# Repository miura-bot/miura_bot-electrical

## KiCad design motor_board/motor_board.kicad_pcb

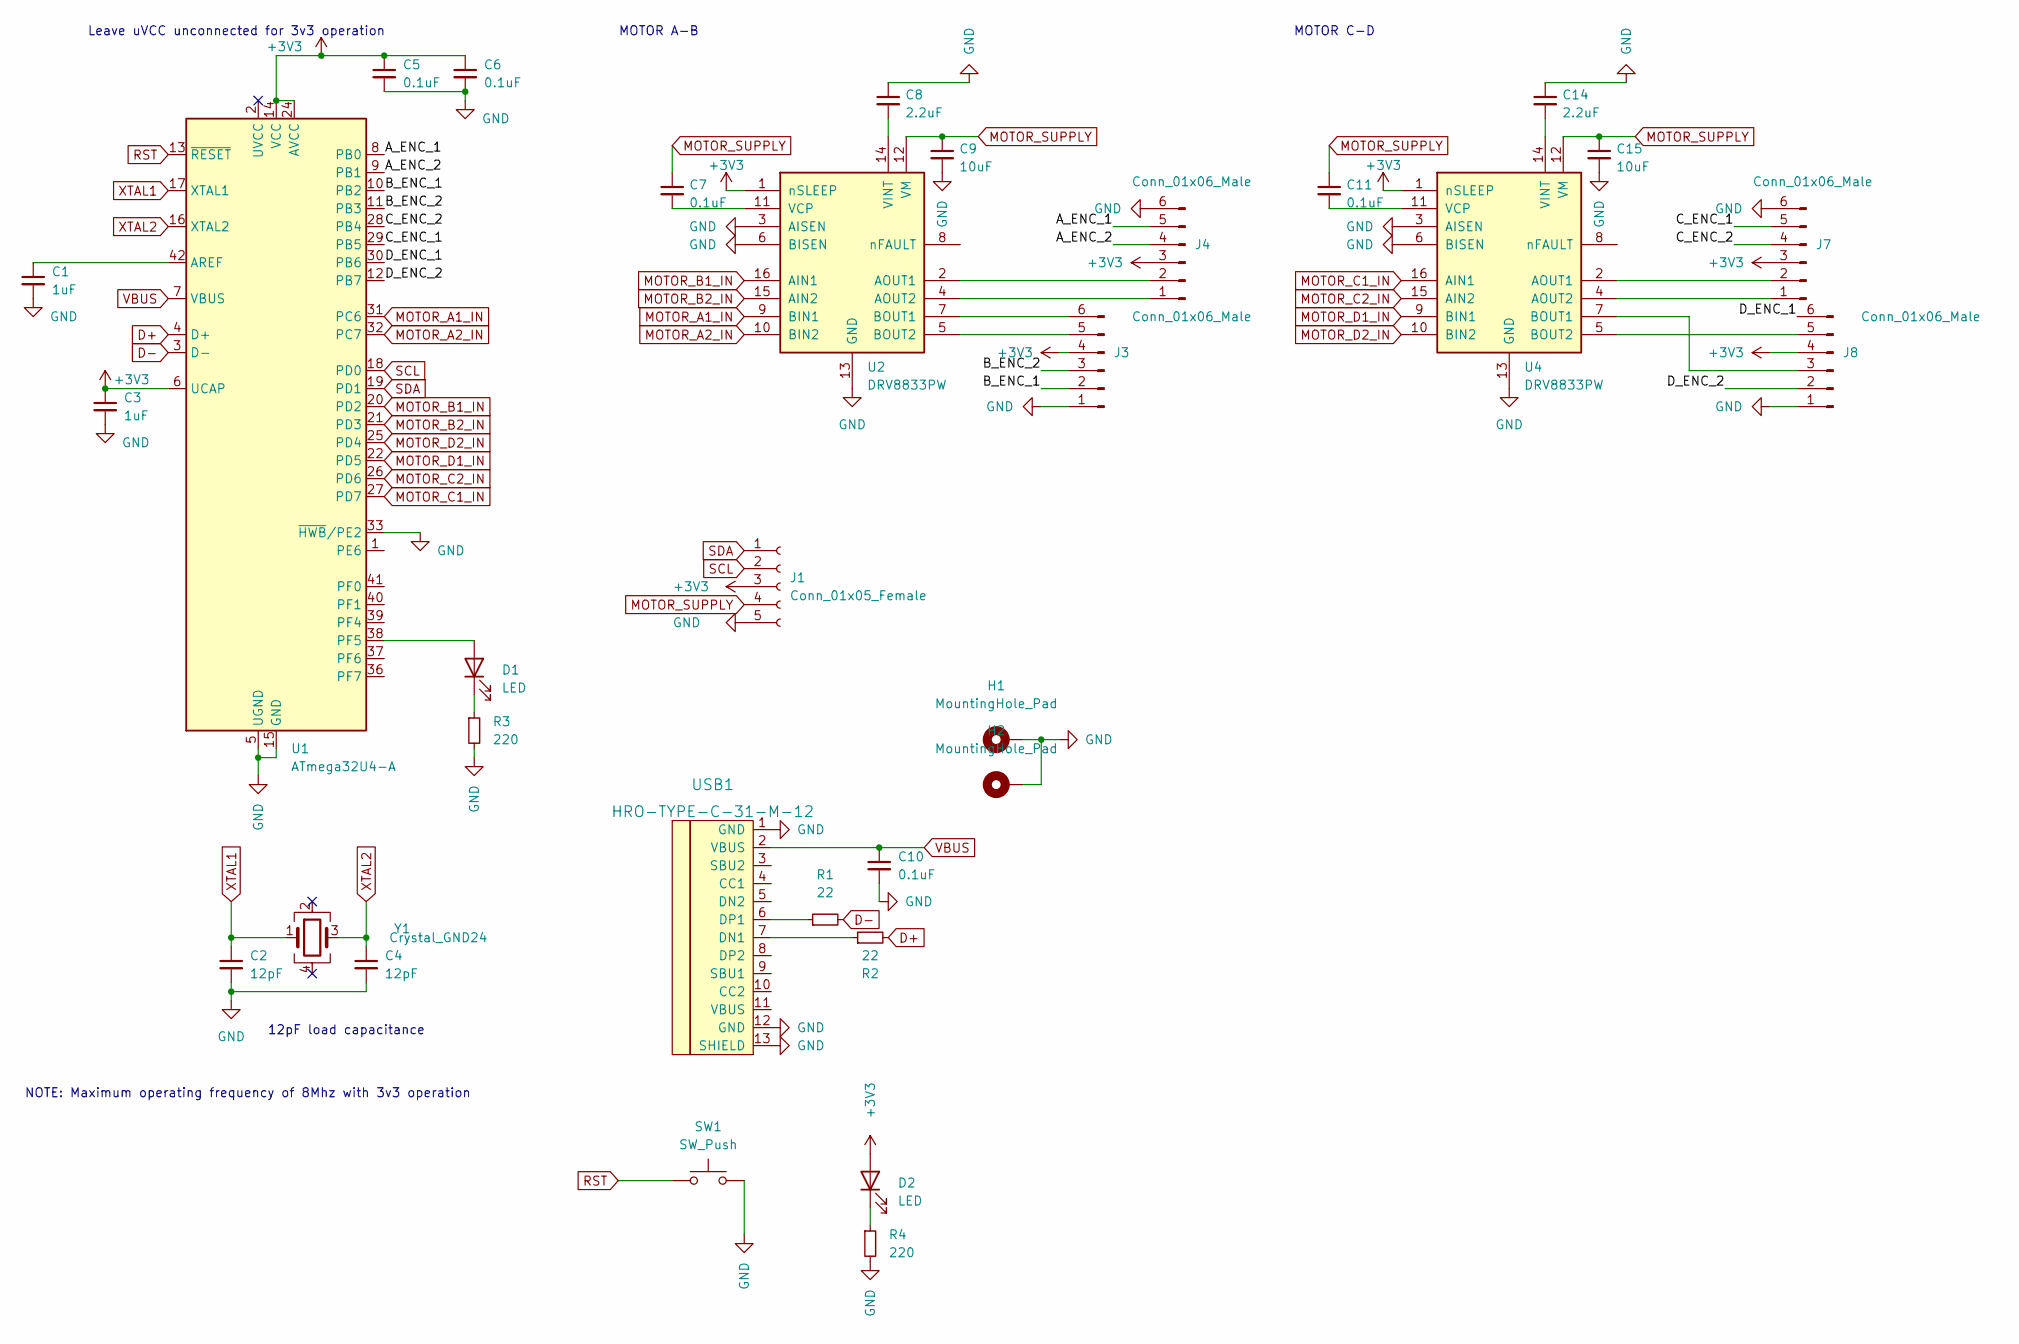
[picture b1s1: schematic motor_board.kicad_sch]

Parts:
C1, C3: 1uF; C_0402_1005Metric; LCSC C106254
C2, C4: 12pF; C_0402_1005Metric; LCSC C106201
C5, C6, C7, C10, C11: 0.1uF; C_0402_1005Metric; LCSC C141382
C8, C14: 2.2uF; C_0402_1005Metric; LCSC C76594
C9, C15: 10uF; C_0402_1005Metric; LCSC C87148
D1, D2: LED; LED_0402_1005Metric; LCSC C273598
H1, H2: MountingHole_Pad; MountingHole_2.2mm_M2_DIN965_Pad
J1: Conn_01x05_Female; PinHeader_1x05_P1.27mm_Vertical
J3, J4, J7, J8: Conn_01x06_Male; PinHeader_1x06_P1.27mm_Vertical
R1, R2: 22; R_0402_1005Metric; LCSC C881322
R3, R4: 220; R_0402_1005Metric; LCSC C881401
SW1: SW_Push; SW_SPST_EVPBF
U1: ATmega32U4-A; TQFP-44_10x10mm_P0.8mm; LCSC C112161
U2, U4: DRV8833PW; TSSOP-16_4.4x5mm_P0.65mm; LCSC C50506
USB1: HRO-TYPE-C-31-M-12; LCSC C165948
Y1: Crystal_GND24; Crystal_SMD_3225-4Pin_3.2x2.5mm; LCSC C253723

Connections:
+3V3: C3.1, C5.1, C6.1, D2.2 (A), J1.3, J3.4, J4.3, J7.3, J8.4, U1.6 (UCAP), U1.14 (VCC), U1.24 (AVCC), U1.34 (VCC), U1.44 (AVCC), U2.1 (nSLEEP), U4.1 (nSLEEP)
/A_ENC_1: J4.5, U1.8 (PB0)
/A_ENC_2: J4.4, U1.9 (PB1)
/B_ENC_1: J3.2, U1.10 (PB2)
/B_ENC_2: J3.3, U1.11 (PB3)
/C_ENC_1: J7.5, U1.29 (PB5)
/C_ENC_2: J7.4, U1.28 (PB4)
/D_ENC_1: J8.6, U1.30 (PB6)
/D_ENC_2: J8.2, U1.12 (PB7)
D+: R2.2, U1.4 (D+)
D-: R1.2, U1.3 (D-)
GND: C1.2, C2.2, C3.2, C4.2, C5.2, C6.2, C8.1, C9.2, C10.2, C14.1, C15.2, H1.1, H2.1, J1.5, J3.1, J4.6, J7.6, J8.1, R3.2, R4.2, SW1.2, U1.5 (UGND), U1.15 (GND), U1.23 (GND), U1.33 (~HWB/PE2), U1.35 (GND), U1.43 (GND), U2.3 (AISEN), U2.6 (BISEN), U2.13 (GND), U4.3 (AISEN), U4.6 (BISEN), U4.13 (GND), USB1.1 (GND), USB1.12 (GND), USB1.13 (SHIELD)
MOTOR_A1_IN: U1.31 (PC6), U2.9 (BIN1)
MOTOR_A2_IN: U1.32 (PC7), U2.10 (BIN2)
MOTOR_B1_IN: U1.20 (PD2), U2.16 (AIN1)
MOTOR_B2_IN: U1.21 (PD3), U2.15 (AIN2)
MOTOR_C1_IN: U1.27 (PD7), U4.16 (AIN1)
MOTOR_C2_IN: U1.26 (PD6), U4.15 (AIN2)
MOTOR_D1_IN: U1.22 (PD5), U4.9 (BIN1)
MOTOR_D2_IN: U1.25 (PD4), U4.10 (BIN2)
MOTOR_SUPPLY: C7.1, C9.1, C11.1, C15.1, J1.4, U2.12 (VM), U4.12 (VM)
unnamed: C1.1, U1.42 (AREF)
unnamed: C7.2, U2.11 (VCP)
unnamed: C8.2, U2.14 (VINT)
unnamed: C11.2, U4.11 (VCP)
unnamed: C14.2, U4.14 (VINT)
unnamed: D1.1 (K), R3.1
unnamed: D1.2 (A), U1.38 (PF5)
unnamed: D2.1 (K), R4.1
unnamed: J3.5, U2.5 (BOUT2)
unnamed: J3.6, U2.7 (BOUT1)
unnamed: J4.1, U2.4 (AOUT2)
unnamed: J4.2, U2.2 (AOUT1)
unnamed: J7.1, U4.4 (AOUT2)
unnamed: J7.2, U4.2 (AOUT1)
unnamed: J8.3, U4.7 (BOUT1)
unnamed: J8.5, U4.5 (BOUT2)
unnamed: R1.1, USB1.6 (DP1)
unnamed: R2.1, USB1.7 (DN1)
RST: SW1.1, U1.13 (~RESET)
SCL: J1.2, U1.18 (PD0)
SDA: J1.1, U1.19 (PD1)
VBUS: C10.1, U1.7 (VBUS), USB1.2 (VBUS)
XTAL1: C2.1, U1.17 (XTAL1), Y1.1
XTAL2: C4.1, U1.16 (XTAL2), Y1.3

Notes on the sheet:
12pF load capacitance
MOTOR C-D
Leave uVCC unconnected for 3v3 operation
NOTE: Maximum operating frequency of 8Mhz with 3v3 operation
MOTOR A-B

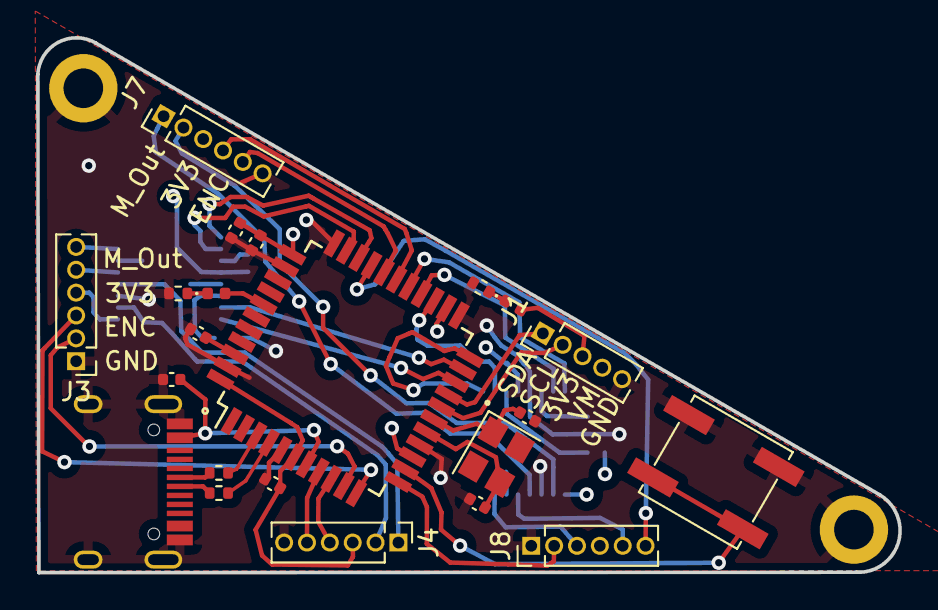
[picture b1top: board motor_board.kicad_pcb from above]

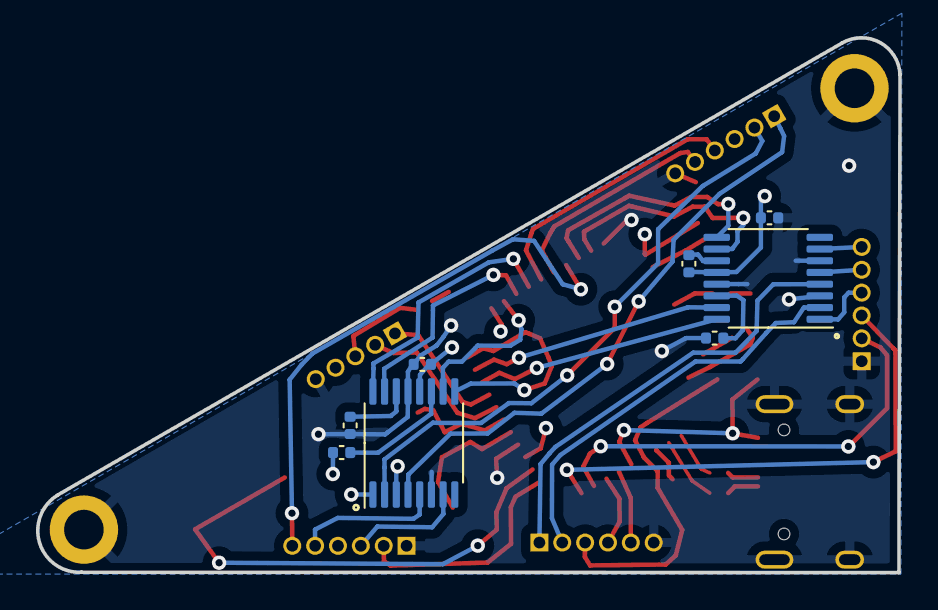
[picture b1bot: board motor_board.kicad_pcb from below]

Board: 4 copper layers, 47.9 x 29.7 mm, 32 parts (8 on the bottom side), 45 nets.

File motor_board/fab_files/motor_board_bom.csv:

Comment,Designator,Footprint,LCSC
"1uF","C1,C3","Capacitor_SMD:C_0402_1005Metric","C106254"
"12pF","C2,C4","Capacitor_SMD:C_0402_1005Metric","C106201"
"0.1uF","C5,C6,C7,C10,C11","Capacitor_SMD:C_0402_1005Metric","C141382"
"2.2uF","C8,C14","Capacitor_SMD:C_0402_1005Metric","C76594"
"10uF","C9,C15","Capacitor_SMD:C_0402_1005Metric","C87148"
"LED","D1,D2","LED_SMD:LED_0402_1005Metric","C273598"
"MountingHole_Pad","H1,H2","MountingHole:MountingHole_2.2mm_M2_DIN965_Pad",""
"Conn_01x05_Female","J1","Connector_PinHeader_1.27mm:PinHeader_1x05_P1.27mm_Vertical",""
"Conn_01x06_Male","J3,J4,J7,J8","Connector_PinHeader_1.27mm:PinHeader_1x06_P1.27mm_Vertical",""
"22","R1,R2","Resistor_SMD:R_0402_1005Metric","C881322"
"220","R3,R4","Resistor_SMD:R_0402_1005Metric","C881401"
"SW_Push","SW1","Button_Switch_SMD:SW_SPST_EVPBF",""
"ATmega32U4-A","U1","Package_QFP:TQFP-44_10x10mm_P0.8mm","C112161"
"DRV8833PW","U2,U4","Package_SO:TSSOP-16_4.4x5mm_P0.65mm","C50506"
"HRO-TYPE-C-31-M-12","USB1","Type-C:HRO-TYPE-C-31-M-12","C165948"
"Crystal_GND24","Y1","Crystal:Crystal_SMD_3225-4Pin_3.2x2.5mm","C253723"

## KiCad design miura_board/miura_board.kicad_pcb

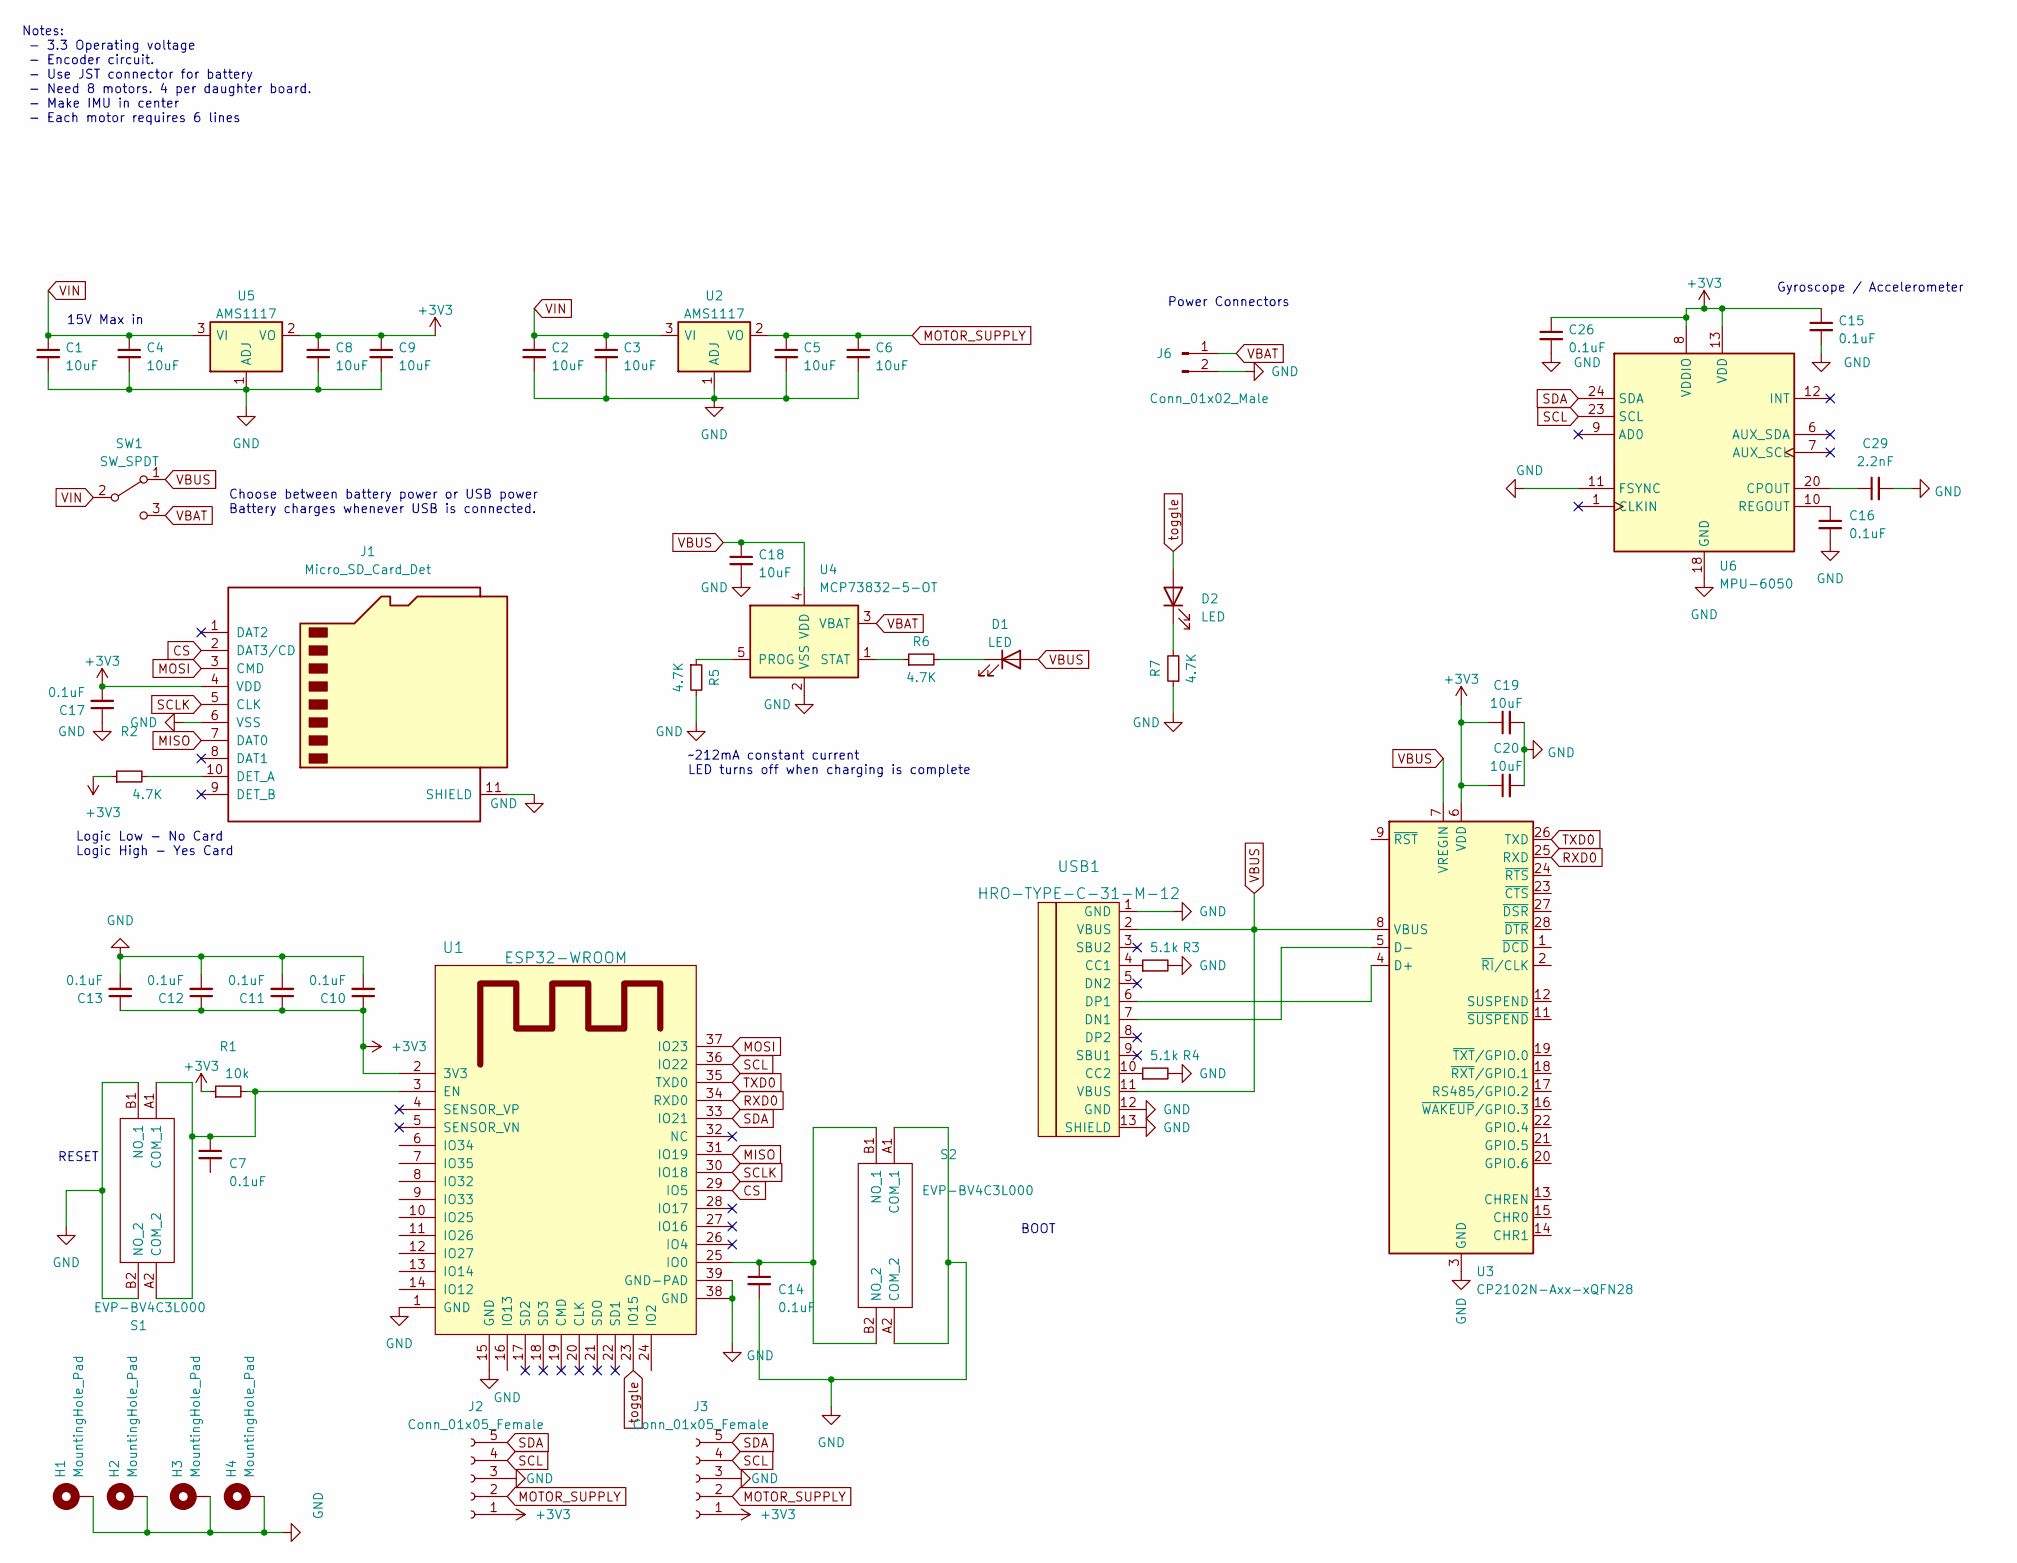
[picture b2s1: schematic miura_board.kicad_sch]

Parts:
C1, C2, C3, C4, C5, C6, C8, C9, C18, C19, C20: 10uF; C_0603_1608Metric
C7, C10, C11, C12, C13, C14, C15, C16, C17, C26: 0.1uF; C_0603_1608Metric
C29: 2.2nF; C_0603_1608Metric
D1, D2: LED; D_0603_1608Metric
H1, H2, H3, H4: MountingHole_Pad; MountingHole_2.2mm_M2_DIN965_Pad
J1: Micro_SD_Card_Det; microSD_HC_Molex_104031-0811; LCSC C585350
J2, J3: Conn_01x05_Female; PinHeader_1x05_P1.27mm_Vertical
J6: Conn_01x02_Male; JST-PH-2-SMT-RA
R1: 10k; R_0603_1608Metric_Pad0.98x0.95mm_HandSolder
R2, R5, R6, R7: 4.7K; R_0603_1608Metric
R3, R4: 5.1k; R_0603_1608Metric_Pad0.98x0.95mm_HandSolder
S1, S2: EVP-BV4C3L000; EVPBV4C3L000; Mouser Part Number 667-EVP-BV4C3L000
SW1: SW_SPDT; SW_SPDT_CK-JS102011SAQN
U1: ESP32-WROOM
U2, U5: AMS1117; SOT-223-3_TabPin2
U3: CP2102N-Axx-xQFN28; QFN-28-1EP_5x5mm_P0.5mm_EP3.35x3.35mm; LCSC C6568
U4: MCP73832-5-OT; SOT-23-5
U6: MPU-6050; InvenSense_QFN-24_4x4mm_P0.5mm; LCSC C24112
USB1: HRO-TYPE-C-31-M-12; LCSC C165948

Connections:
+3V3: C8.1, C9.1, C10.1, C11.1, C12.1, C13.1, C15.1, C17.2, C19.1, C20.1, C26.1, J1.4 (VDD), J2.1, J3.1, R1.1, R2.1, U1.2 (3V3), U3.6 (VDD), U5.2 (VO), U6.8 (VDDIO), U6.13 (VDD)
CS: J1.2 (DAT3/CD), U1.29 (IO5)
GND: C1.2, C2.2, C3.2, C4.2, C5.2, C6.2, C8.2, C9.2, C10.2, C11.2, C12.2, C13.2, C14.2, C15.2, C16.2, C17.1, C18.2, C19.2, C20.2, C26.2, C29.2, H1.1, H2.1, H3.1, H4.1, J1.6 (VSS), J1.11 (SHIELD), J2.3, J3.3, J6.2, R3.2, R4.2, R5.2, R7.1, S1.B1 (NO_1), S1.B2 (NO_2), S2.A1 (COM_1), S2.A2 (COM_2), U1.1 (GND), U1.15 (GND), U1.38 (GND), U1.39 (GND-PAD), U2.1 (ADJ), U3.3 (GND), U3.29 (GND), U4.2 (VSS), U5.1 (ADJ), U6.11 (FSYNC), U6.18 (GND), USB1.1 (GND), USB1.12 (GND), USB1.13 (SHIELD)
MISO: J1.7 (DAT0), U1.31 (IO19)
MOSI: J1.3 (CMD), U1.37 (IO23)
MOTOR_SUPPLY: C5.1, C6.1, J2.2, J3.2, U2.2 (VO)
unnamed: C7.1, R1.2, S1.A1 (COM_1), S1.A2 (COM_2), U1.3 (EN)
unnamed: C14.1, S2.B1 (NO_1), S2.B2 (NO_2), U1.25 (IO0)
unnamed: C16.1, U6.10 (REGOUT)
unnamed: C29.1, U6.20 (CPOUT)
unnamed: D1.1 (K), R6.2
unnamed: D2.1 (K), R7.2
unnamed: J1.10 (DET_A), R2.2
unnamed: R3.1, USB1.4 (CC1)
unnamed: R4.1, USB1.10 (CC2)
unnamed: R5.1, U4.5 (PROG)
unnamed: R6.1, U4.1 (STAT)
unnamed: U3.4 (D+), USB1.6 (DP1)
unnamed: U3.5 (D-), USB1.7 (DN1)
RXD0: U1.34 (RXD0), U3.25 (RXD)
SCL: J2.4, J3.4, U1.36 (IO22), U6.23 (SCL)
SCLK: J1.5 (CLK), U1.30 (IO18)
SDA: J2.5, J3.5, U1.33 (IO21), U6.24 (SDA)
TXD0: U1.35 (TXD0), U3.26 (TXD)
VBAT: J6.1, SW1.3 (C), U4.3 (VBAT)
VBUS: C18.1, D1.2 (A), SW1.1 (A), U3.7 (VREGIN), U3.8 (VBUS), U4.4 (VDD), USB1.2 (VBUS), USB1.11 (VBUS)
VIN: C1.1, C2.1, C3.1, C4.1, SW1.2 (B), U2.3 (VI), U5.3 (VI)
toggle: D2.2 (A), U1.23 (IO15)

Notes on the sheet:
Choose between battery power or USB power Battery charges whenever USB is connected.
Gyroscope / Accelerometer
Notes: - 3.3 Operating voltage - Encoder circuit. - Use JST connector for battery - Need 8 motors. 4 per daughter board. - Make IMU in center - Each motor requires 6 lines
RESET
15V Max in
Logic Low - No Card Logic High - Yes Card
Power Connectors
BOOT
~212mA constant current LED turns off when charging is complete

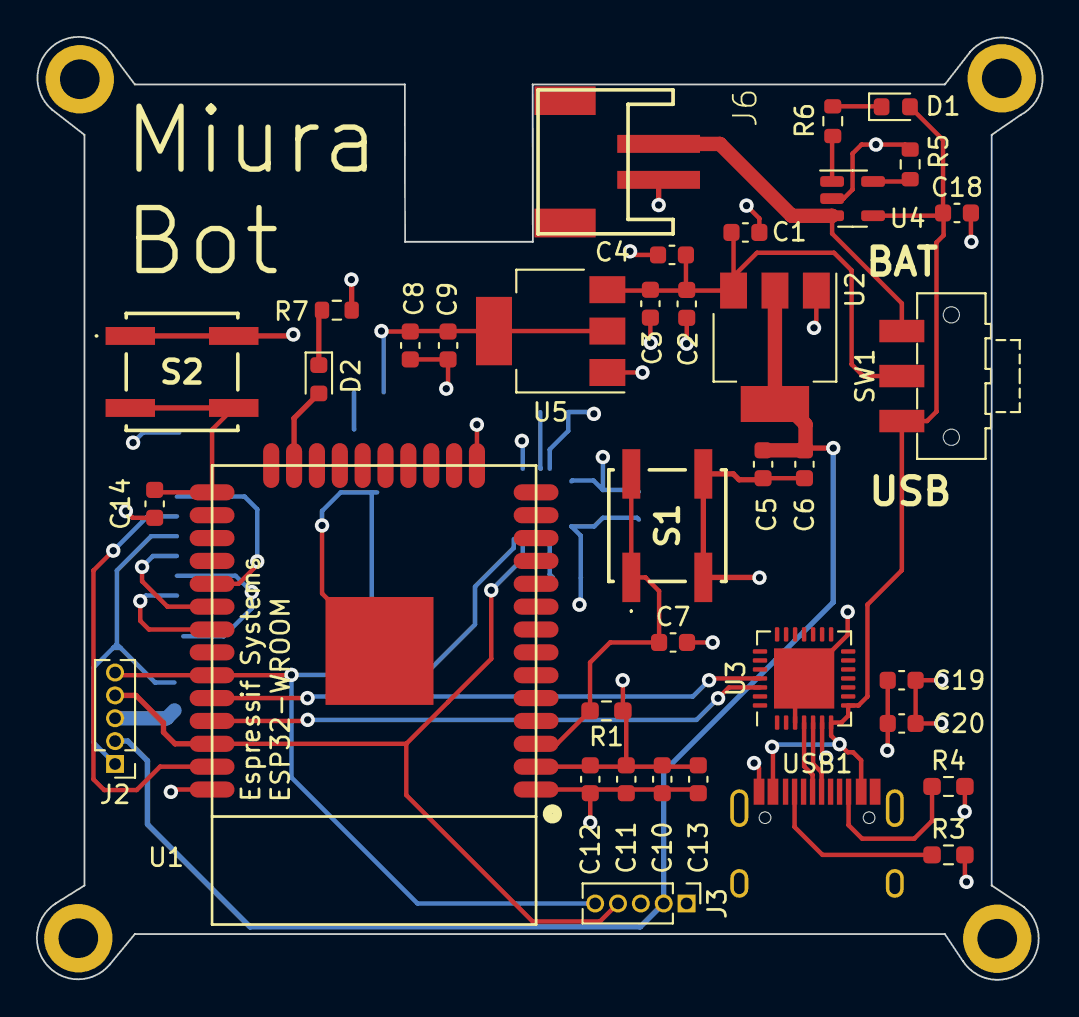
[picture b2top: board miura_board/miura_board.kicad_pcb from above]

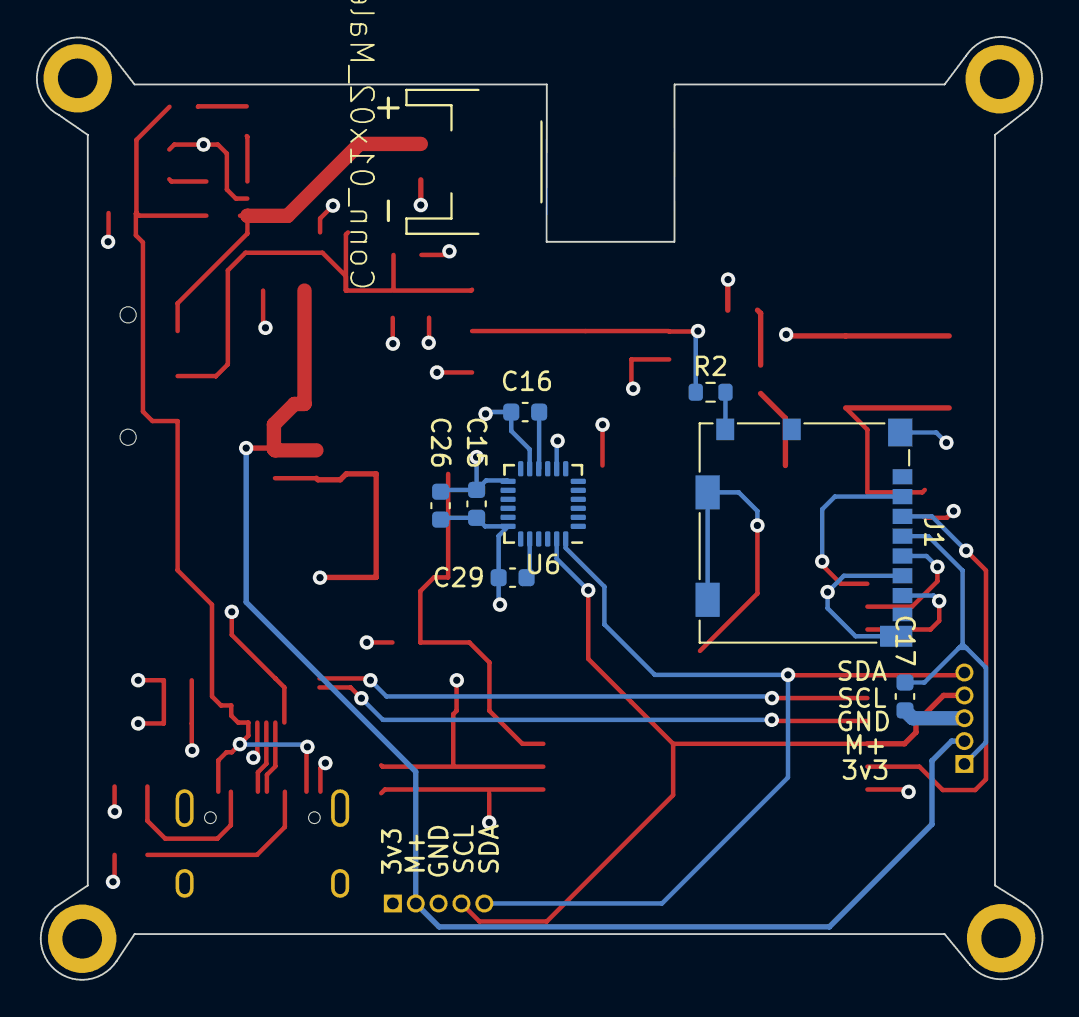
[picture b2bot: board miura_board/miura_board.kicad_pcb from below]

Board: 4 copper layers, 55.9 x 52.4 mm, 49 parts (8 on the bottom side), 28 nets.

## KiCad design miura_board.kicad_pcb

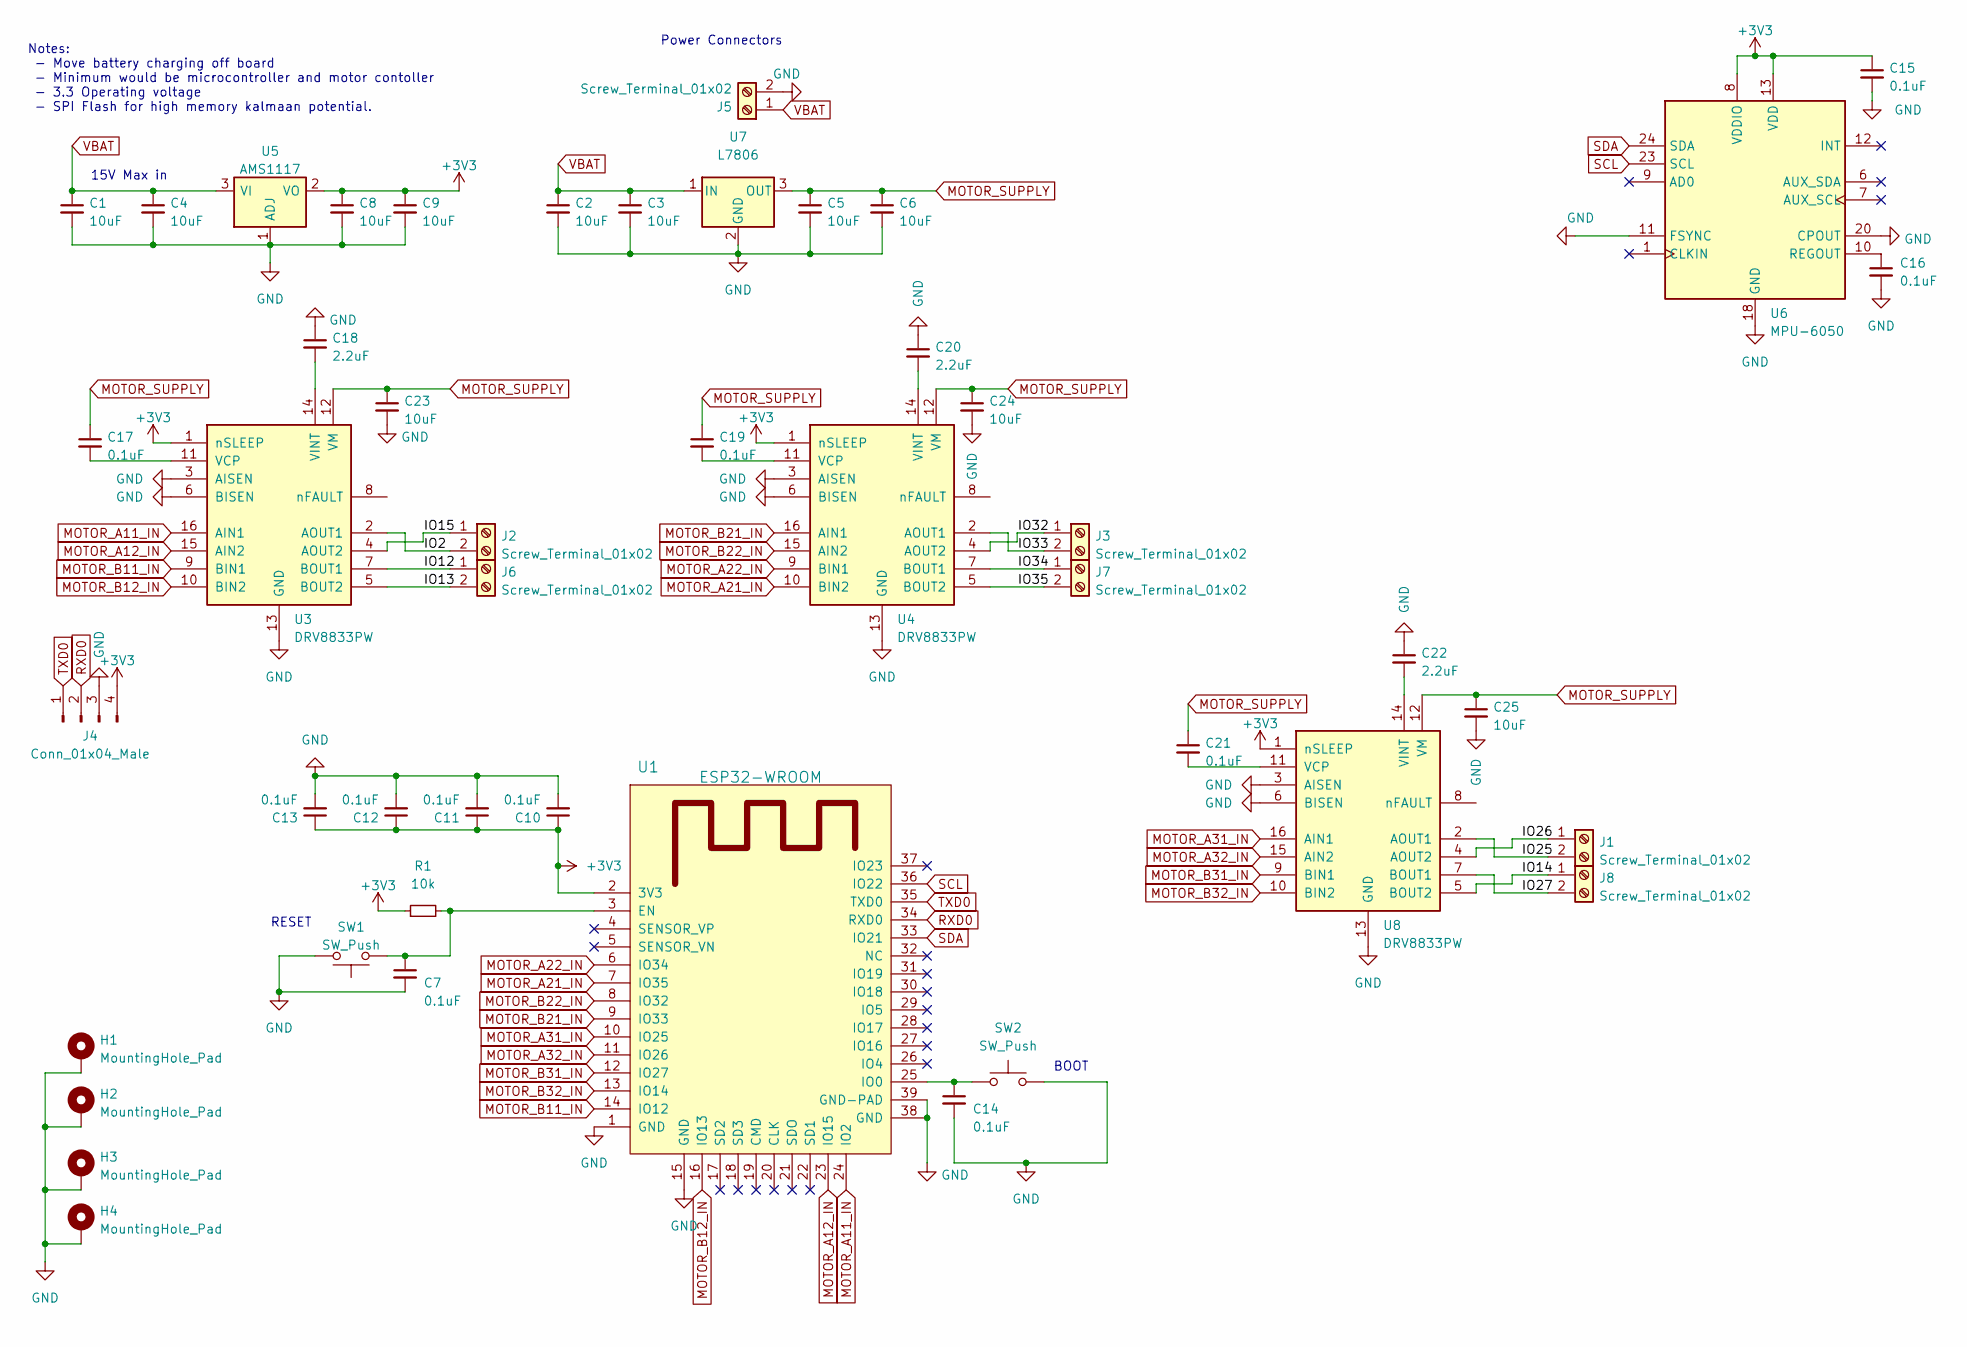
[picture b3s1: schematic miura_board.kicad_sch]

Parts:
C1, C2, C3, C4, C5, C6, C8, C9, C23, C24, C25: 10uF; C_0603_1608Metric
C7, C10, C11, C12, C13, C14, C15, C16, C17, C19, C21: 0.1uF; C_0603_1608Metric
C18, C20, C22: 2.2uF; C_0603_1608Metric
H1, H2, H3, H4: MountingHole_Pad; MountingHole_2.2mm_M2_DIN965_Pad
J1, J2, J3, J5, J6, J7, J8: Screw_Terminal_01x02; TerminalBlock_Phoenix_MPT-0,5-2-2.54_1x02_P2.54mm_Horizontal
J4: Conn_01x04_Male; PinHeader_1x04_P2.54mm_Vertical
R1: 10k; R_0603_1608Metric_Pad0.98x0.95mm_HandSolder
SW1, SW2: SW_Push; SW_SPST_EVPBF
U1: ESP32-WROOM
U3, U4, U8: DRV8833PW; TSSOP-16_4.4x5mm_P0.65mm
U5: AMS1117; SOT-223-3_TabPin2
U6: MPU-6050; InvenSense_QFN-24_4x4mm_P0.5mm
U7: L7806; TO-252-3_TabPin2

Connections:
+3V3: C8.1, C9.1, C10.1, C11.1, C12.1, C13.1, C15.1, J4.4, R1.1, U1.2 (3V3), U3.1 (nSLEEP), U4.1 (nSLEEP), U5.2 (VO), U6.8 (VDDIO), U6.13 (VDD), U8.1 (nSLEEP)
/IO2: J2.2, U3.2 (AOUT1)
/IO12: J6.1, U3.7 (BOUT1)
/IO13: J6.2, U3.5 (BOUT2)
/IO14: J8.1, U8.5 (BOUT2)
/IO15: J2.1, U3.4 (AOUT2)
/IO25: J1.2, U8.2 (AOUT1)
/IO26: J1.1, U8.4 (AOUT2)
/IO27: J8.2, U8.7 (BOUT1)
/IO32: J3.1, U4.4 (AOUT2)
/IO33: J3.2, U4.2 (AOUT1)
/IO34: J7.1, U4.7 (BOUT1)
/IO35: J7.2, U4.5 (BOUT2)
GND: C1.2, C2.2, C3.2, C4.2, C5.2, C6.2, C7.2, C8.2, C9.2, C10.2, C11.2, C12.2, C13.2, C14.2, C15.2, C16.2, C18.1, C20.1, C22.1, C23.2, C24.2, C25.2, H1.1, H2.1, H3.1, H4.1, J4.3, J5.2, SW1.2, SW2.2, U1.1 (GND), U1.15 (GND), U1.38 (GND), U1.39 (GND-PAD), U3.3 (AISEN), U3.6 (BISEN), U3.13 (GND), U4.3 (AISEN), U4.6 (BISEN), U4.13 (GND), U5.1 (ADJ), U6.11 (FSYNC), U6.18 (GND), U6.20 (CPOUT), U7.2 (GND), U8.3 (AISEN), U8.6 (BISEN), U8.13 (GND)
MOTOR_A11_IN: U1.24 (IO2), U3.16 (AIN1)
MOTOR_A12_IN: U1.23 (IO15), U3.15 (AIN2)
MOTOR_A21_IN: U1.7 (IO35), U4.10 (BIN2)
MOTOR_A22_IN: U1.6 (IO34), U4.9 (BIN1)
MOTOR_A31_IN: U1.10 (IO25), U8.16 (AIN1)
MOTOR_A32_IN: U1.11 (IO26), U8.15 (AIN2)
MOTOR_B11_IN: U1.14 (IO12), U3.9 (BIN1)
MOTOR_B12_IN: U1.16 (IO13), U3.10 (BIN2)
MOTOR_B21_IN: U1.9 (IO33), U4.16 (AIN1)
MOTOR_B22_IN: U1.8 (IO32), U4.15 (AIN2)
MOTOR_B31_IN: U1.12 (IO27), U8.9 (BIN1)
MOTOR_B32_IN: U1.13 (IO14), U8.10 (BIN2)
MOTOR_SUPPLY: C5.1, C6.1, C17.1, C19.1, C21.1, C23.1, C24.1, C25.1, U3.12 (VM), U4.12 (VM), U7.3 (OUT), U8.12 (VM)
unnamed: C7.1, R1.2, SW1.1, U1.3 (EN)
unnamed: C14.1, SW2.1, U1.25 (IO0)
unnamed: C16.1, U6.10 (REGOUT)
unnamed: C17.2, U3.11 (VCP)
unnamed: C18.2, U3.14 (VINT)
unnamed: C19.2, U4.11 (VCP)
unnamed: C20.2, U4.14 (VINT)
unnamed: C21.2, U8.11 (VCP)
unnamed: C22.2, U8.14 (VINT)
RXD0: J4.2, U1.34 (RXD0)
SCL: U1.36 (IO22), U6.23 (SCL)
SDA: U1.33 (IO21), U6.24 (SDA)
TXD0: J4.1, U1.35 (TXD0)
VBAT: C1.1, C2.1, C3.1, C4.1, J5.1, U5.3 (VI), U7.1 (IN)

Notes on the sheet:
Notes: - Move battery charging off board - Minimum would be microcontroller and motor contoller - 3.3 Operating voltage - SPI Flash for high memory kalmaan potential.
RESET
15V Max in
Power Connectors
BOOT

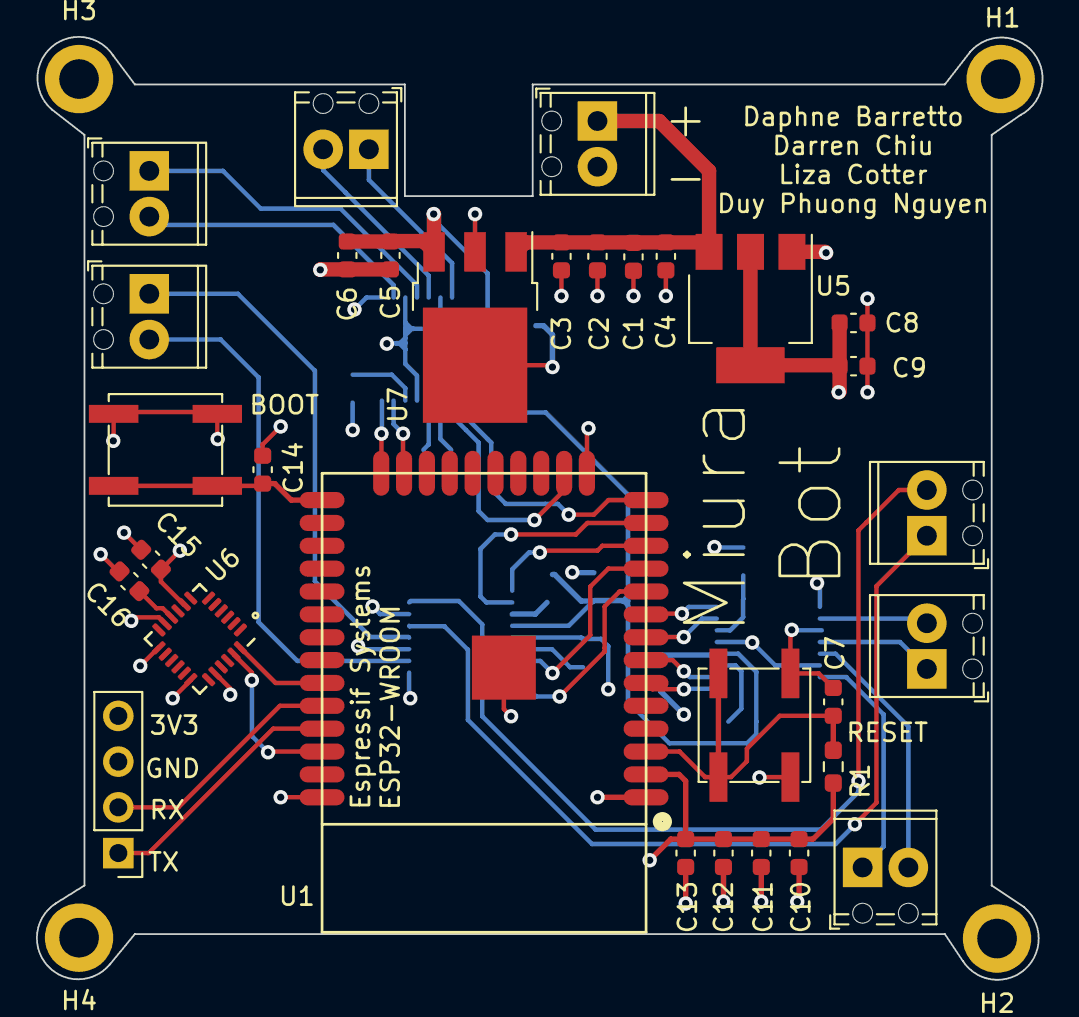
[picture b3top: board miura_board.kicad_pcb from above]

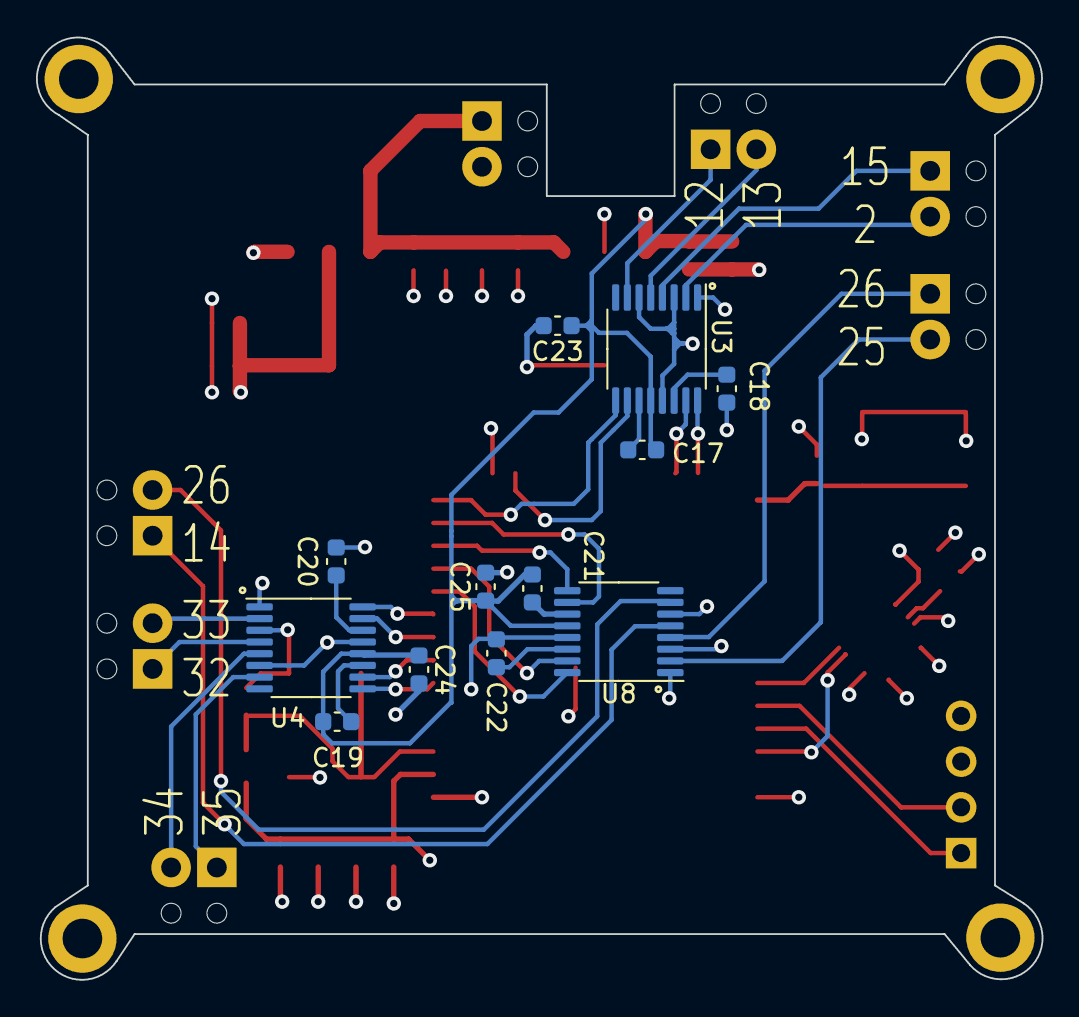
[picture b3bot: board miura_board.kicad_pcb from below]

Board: 4 copper layers, 55.9 x 52.4 mm, 47 parts (12 on the bottom side), 41 nets.

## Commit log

2022-10-25 Initial Board Design
2022-10-25 Corners
2022-10-26 Square
2022-10-26 Added ESP32
2022-10-27 STEP
2022-10-28 Verify sch and begin route
2022-10-29 Need to route SPI
2022-10-29 Finished board
2022-10-29 Added more silk
2022-10-29 Measurements
2022-10-29 Ordered board, removed SPI flash
2022-10-29 New render lol
2022-11-27 Working motor controller
2022-11-27 new board design
2022-11-27 Add bypass
2023-01-27 new version
2023-01-27 four layer
2023-02-09 Adding duaghter board
2023-02-13 Rehaul
2023-02-13 Routing done
2023-02-13 Added switch
2023-02-14 Order ready
2023-02-22 gaaahhh
2023-02-24 im so tired
2023-03-01 Added daughter board
2023-03-10 Ordered motor board
2023-03-22 Fixed multipled pours on same plane
2023-03-26 Recent JLC order for motor controllers
